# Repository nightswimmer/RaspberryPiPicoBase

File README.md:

# Raspberry Pi Pico Base

A KiCad 10 base design for a custom **RP2354A** board (the RP2350 variant with
2 MB of flash inside the package): everything the chip needs to boot and run
reliably, and nothing else. Fork it, add your own circuitry to the free GPIO,
and order it assembled at JLCPCB.

The design is derived from the official Raspberry Pi
*RP2350A QFN-60 Minimal Design Example* (revision R4-S1, July 2026, MIT
licence, see [NOTICE.md](NOTICE.md)). The external QSPI flash section was
removed because the RP2354A has flash on board, the Micro-USB connector was
replaced by USB-C, and the bill of materials was reworked around JLCPCB's
parts library. The project is self-contained (project-local symbol and
footprint libraries with embedded 3D models) and ERC and DRC pass with zero
violations.

## What is on the board

| Block | Parts |
|---|---|
| MCU | RP2354A (QFN-60, 2 MB internal flash), 12 MHz crystal (YXC X322512MSB4SI, 20 pF) with 33 pF load caps, 1 kΩ series resistor on XOUT. QSPI data/clock pins unused; QSPI_SS kept for BOOTSEL |
| Power | AMS1117-3.3 LDO from USB VBUS, on-chip switching regulator with 3.3 µH inductor for the 1.1 V core, 100 nF decoupling on every supply pin, 33 Ω / 4.7 µF filter on VREG_AVDD |
| USB | USB-C receptacle (Korean Hroparts TYPE-C-31-M-12, USB 2.0), 5.1 kΩ CC pull-downs, 27 Ω series resistors on D+/D- |
| Buttons | BOOTSEL and RUN tactile switches (XKB TS-1187A-B-A-B, 5.1 mm) |
| Debug | 3-pin JST GH SWD connector (Raspberry Pi Debug Probe pinout), not populated by default; SWD/SWCLK are also on the J3 header |
| I/O | Two 2x18 2.54 mm pin headers breaking out all 30 GPIO, 3V3, 1V1 and GND |
| Mechanical | 4 x 2.75 mm mounting holes |

## Bill of materials for JLCPCB

Every part carries its LCSC code (`lcsc_pn` field) and the design uses JLCPCB
*Basic* parts wherever a drop-in exists; the remaining *Extended* parts are the
RP2354A, the inductor, the USB-C connector, the 27 Ω USB resistors and the pin
headers. [docs/BOM.md](docs/BOM.md) has the full sourcing table with
Basic/Extended status, the alternatives that were considered and how to
regenerate the order files. Ready-made files:

- [bom/bom.csv](bom/bom.csv): grouped BOM with designators, quantities and LCSC part numbers
- [bom/cpl.csv](bom/cpl.csv): component placement (DNP parts excluded)

The original Raspberry Pi BOM is in
[docs/reference/RPI-RP2350A-MINIMAL_R4-S1_BOM.md](docs/reference/RPI-RP2350A-MINIMAL_R4-S1_BOM.md)
and the original schematic PDF is next to it.

## Repository layout

```
RaspberryPiPicoBase.kicad_pro   KiCad 10 project
RaspberryPiPicoBase.kicad_sch   schematic (single sheet)
RaspberryPiPicoBase.kicad_pcb   routed 2-layer board, 3D models embedded
sym-lib-table / fp-lib-table    project-local library tables
lib/RaspberryPiPicoBase.kicad_sym    all symbols used by the design
lib/RaspberryPiPicoBase.pretty/      all footprints, each with its 3D model embedded
bom/                            JLCPCB BOM and placement files (generated)
docs/BOM.md                     sourcing table, part status and alternatives
docs/reference/                 original Raspberry Pi schematic PDF and BOM
.mcp.json                       KiCad MCP server for Claude Code (kicad-mcp-pro)
NOTICE.md                       third-party attribution
```

## Requirements

- KiCad 10.0.x (tested with 10.0.8 on Windows 11). No global library setup is
  needed: every symbol, footprint and 3D model lives in this repository.

## Checking the design from the command line

```
kicad-cli sch erc --severity-all RaspberryPiPicoBase.kicad_sch
kicad-cli pcb drc --severity-all --schematic-parity --refill-zones RaspberryPiPicoBase.kicad_pcb
```

Both report zero violations on the base design. The only entries are four
pre-excluded `lib_footprint_mismatch` warnings on the mounting holes, a KiCad
false positive caused by the full-circle arc inside that footprint.

## AI-assisted editing with Claude Code (MCP)

The repository ships a project-local `.mcp.json` that starts
[kicad-mcp-pro](https://github.com/oaslananka/kicad-mcp-pro) 4.5.0 through
`uvx`, in the `full` profile with write mode. Claude Code picks it up
automatically when the repository is the working directory.

Prerequisites:

1. [uv](https://docs.astral.sh/uv/) on the PATH (`uvx` downloads the server on first use).
2. KiCad 10 installed in the default location (kicad-cli is auto-detected).
3. In KiCad: *Preferences > Plugins > Enable KiCad API*, then restart KiCad.

How edits reach KiCad, and what that means for your workflow: tools edit the
`.kicad_sch`, `.kicad_pcb` and library files on disk and verify them with
`kicad-cli`. KiCad does not notice edits made on disk while a file is open, so
after an editing session use *File > Revert* (or reopen the project) before
saving anything in KiCad, otherwise the on-disk changes are overwritten.

## Licence

The project files in this repository are MIT licensed (see [LICENSE](LICENSE)).
The underlying design is copyright Raspberry Pi Ltd, MIT licensed; the
copied KiCad library footprints and 3D model are CC-BY-SA 4.0 with the KiCad
exception; the EasyEDA/LCSC 3D models are included for visualisation (see
[NOTICE.md](NOTICE.md)).

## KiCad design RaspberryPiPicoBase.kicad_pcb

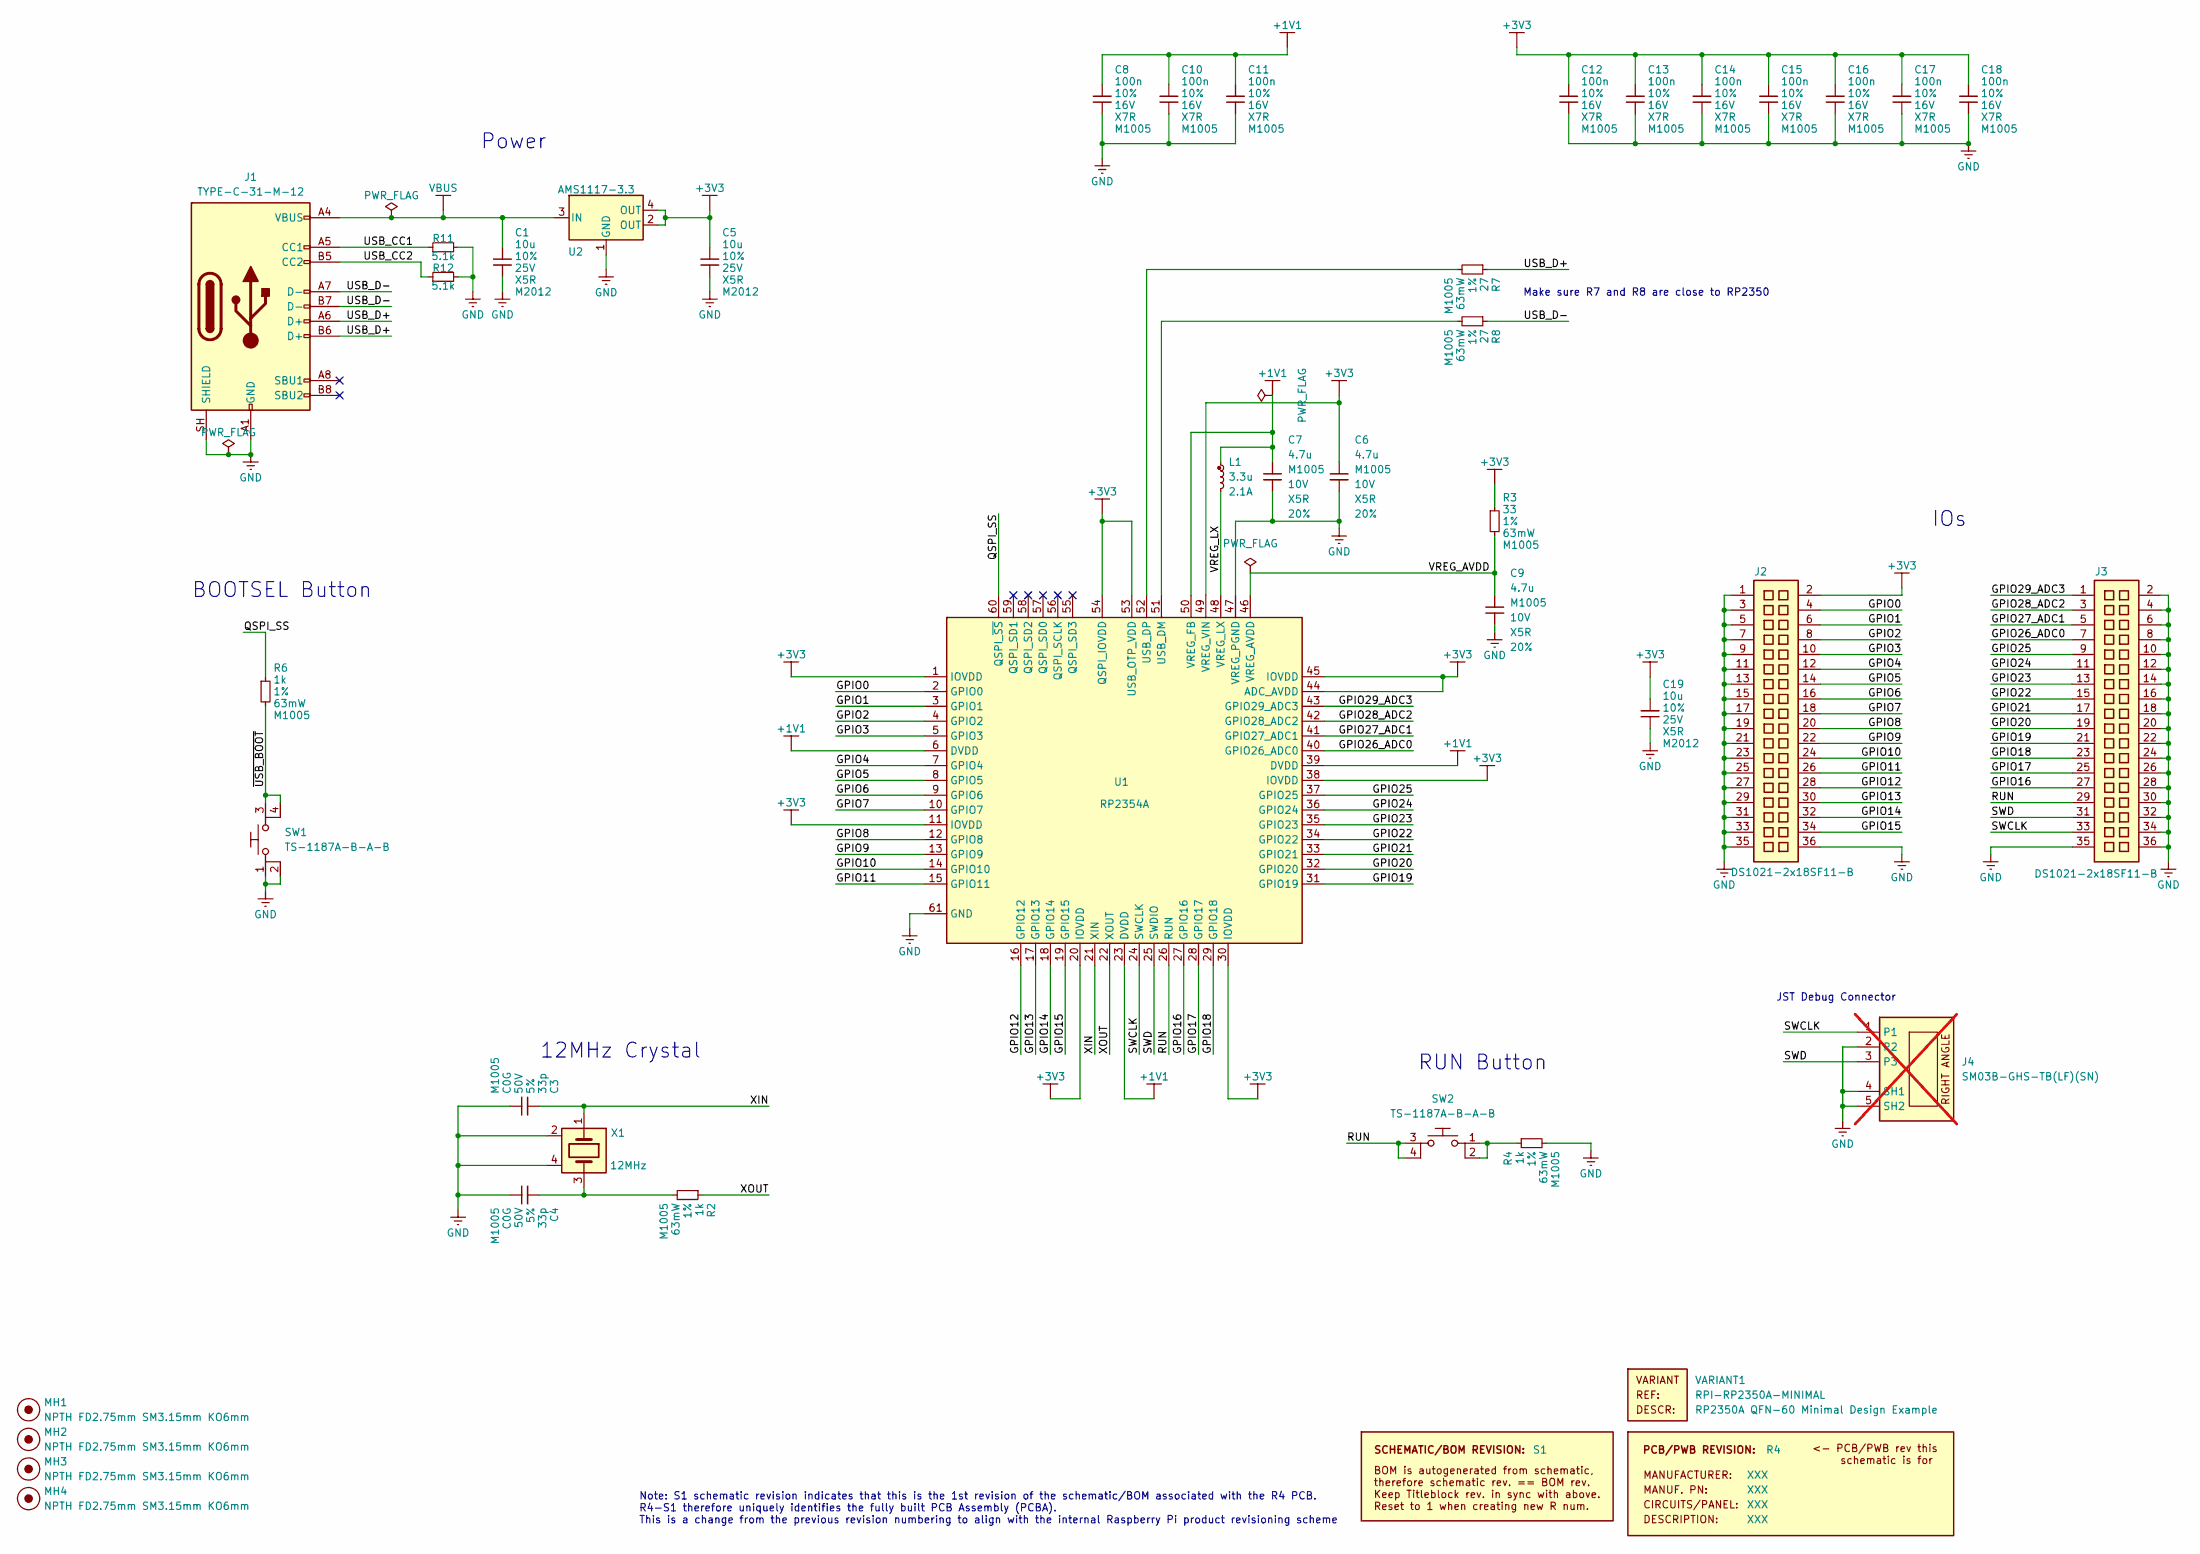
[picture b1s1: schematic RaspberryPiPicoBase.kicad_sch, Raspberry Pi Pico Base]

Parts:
C1, C5, C19: 10u; generic_capc2012x125; voltage 25V; tolerance 10%; part_uid RP-01GYSK-AVBE41; lcsc_pn C15850
C3, C4: 33p; generic_capc1005x50; voltage 50V; tolerance 5%; part_uid RP-01C89W-LLY9XV; lcsc_pn C1562
C6, C7: 4.7u; generic_capc1005x50_wide; voltage 10V; tolerance 20%; part_uid RP-019A1P-0C2GHY; lcsc_pn C23733
C8, C10, C11, C12, C13, C14, C15, C16, C17, C18: 100n; generic_capc1005x50; voltage 16V; tolerance 10%; part_uid RP-01BJ9Y-KRGF41; lcsc_pn C1525
C9: 4.7u; generic_capc1005x50; voltage 10V; tolerance 20%; part_uid RP-019A1P-0C2GHY; lcsc_pn C23733
J1: TYPE-C-31-M-12; USB_C_Receptacle_HRO_TYPE-C-31-M-12; manufacturer_pn TYPE-C-31-M-12; lcsc_pn C165948
J2, J3: DS1021-2x18SF11-B; samtec_tsw-118-07-l-d; part_uid RP-01JWH2-G371Y4; lcsc_pn C7430414
J4: SM03B-GHS-TB(LF)(SN); jst_sm03b-ghs-tb; part_uid RP-01EKJ1-8V9SV1; lcsc_pn C514175; not fitted
L1: 3.3u; abracon_aota-b201610s3r3-101-t; tolerance 20%; part_uid RP-01GY5D-2VC7WP; lcsc_pn C42411119
MH1, MH2, MH3, MH4: NPTH FD2.75mm SM3.15mm KO6mm; none_mh_npth_fd2p75mm_sm3p15mm_ko6mm; part_uid RP-01HF5R-LCTEJS
PCB1: R4; manufacturer_pn XXX
R2, R4, R6: 1k; generic_resc1005x35; tolerance 1%; voltage 50V; part_uid RP-019A1P-4Z6ZWY; lcsc_pn C11702
R3: 33; generic_resc1005x35; tolerance 1%; voltage 50V; part_uid RP-019A1P-58PW9L; lcsc_pn C25105
R7, R8: 27; generic_resc1005x35; tolerance 1%; voltage 50V; part_uid RP-01C89V-LTEYC4; lcsc_pn C25100
R11, R12: 5.1k; generic_resc1005x35; tolerance 1%; manufacturer_pn 0402WGF5101TCE; lcsc_pn C25905
SBREV1: S1
SW1, SW2: TS-1187A-B-A-B; xkb_ts-1187a-b-a-b; part_uid RP-01H0MT-6E9H8F; lcsc_pn C318884
U1: RP2354A; rpi_rp2350a_vias; part_uid RP-01HA9H-9K5E8T; lcsc_pn C41378174
U2: AMS1117-3.3; onsemi_ncp1117st33t3g; voltage 3.3V; part_uid RP-01JWD9-7JRX6J; lcsc_pn C6186
VARIANT1: RPI-RP2350A-MINIMAL
X1: 12MHz; generic_xtalcc320x250x80-4; tolerance 10ppm; part_uid RP-01G8X7-GS352B; lcsc_pn C9002

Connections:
+1V1: C7.1, C8.1, C10.1, C11.1, L1.1, U1.6 (DVDD), U1.23 (DVDD), U1.39 (DVDD), U1.50 (VREG_FB)
+3V3: C5.1, C6.1, C12.1, C13.1, C14.1, C15.1, C16.1, C17.1, C18.1, C19.1, J2.2, R3.1, U1.1 (IOVDD), U1.11 (IOVDD), U1.20 (IOVDD), U1.30 (IOVDD), U1.38 (IOVDD), U1.44 (ADC_AVDD), U1.45 (IOVDD), U1.49 (VREG_VIN), U1.53 (USB_OTP_VDD), U1.54 (QSPI_IOVDD), U2.2 (OUT), U2.4 (OUT)
/GPIO0: J2.4, U1.2 (GPIO0)
/GPIO1: J2.6, U1.3 (GPIO1)
/GPIO2: J2.8, U1.4 (GPIO2)
/GPIO3: J2.10, U1.5 (GPIO3)
/GPIO4: J2.12, U1.7 (GPIO4)
/GPIO5: J2.14, U1.8 (GPIO5)
/GPIO6: J2.16, U1.9 (GPIO6)
/GPIO7: J2.18, U1.10 (GPIO7)
/GPIO8: J2.20, U1.12 (GPIO8)
/GPIO9: J2.22, U1.13 (GPIO9)
/GPIO10: J2.24, U1.14 (GPIO10)
/GPIO11: J2.26, U1.15 (GPIO11)
/GPIO12: J2.28, U1.16 (GPIO12)
/GPIO13: J2.30, U1.17 (GPIO13)
/GPIO14: J2.32, U1.18 (GPIO14)
/GPIO15: J2.34, U1.19 (GPIO15)
/GPIO16: J3.27, U1.27 (GPIO16)
/GPIO17: J3.25, U1.28 (GPIO17)
/GPIO18: J3.23, U1.29 (GPIO18)
/GPIO19: J3.21, U1.31 (GPIO19)
/GPIO20: J3.19, U1.32 (GPIO20)
/GPIO21: J3.17, U1.33 (GPIO21)
/GPIO22: J3.15, U1.34 (GPIO22)
/GPIO23: J3.13, U1.35 (GPIO23)
/GPIO24: J3.11, U1.36 (GPIO24)
/GPIO25: J3.9, U1.37 (GPIO25)
/GPIO26_ADC0: J3.7, U1.40 (GPIO26_ADC0)
/GPIO27_ADC1: J3.5, U1.41 (GPIO27_ADC1)
/GPIO28_ADC2: J3.3, U1.42 (GPIO28_ADC2)
/GPIO29_ADC3: J3.1, U1.43 (GPIO29_ADC3)
/QSPI_SS: R6.1, U1.60 (QSPI_~SS)
/RUN: J3.29, SW2.3, SW2.4, U1.26 (RUN)
/SWCLK: J3.33, J4.1, U1.24 (SWCLK)
/SWD: J3.31, J4.3, U1.25 (SWDIO)
/USB_CC1: J1.A5 (CC1), R11.1
/USB_CC2: J1.B5 (CC2), R12.1
/USB_D+: J1.A6 (D+), J1.B6 (D+), R7.1
/USB_D-: J1.A7 (D-), J1.B7 (D-), R8.1
/VREG_AVDD: C9.1, R3.2, U1.46 (VREG_AVDD)
/VREG_LX: L1.2, U1.48 (VREG_LX)
/XIN: C3.1, U1.21 (XIN), X1.1
/XOUT: R2.1, U1.22 (XOUT)
/~USB_BOOT: R6.2, SW1.3, SW1.4
GND: C1.2, C3.2, C4.2, C5.2, C6.2, C7.2, C8.2, C9.2, C10.2, C11.2, C12.2, C13.2, C14.2, C15.2, C16.2, C17.2, C18.2, C19.2, J1.A1 (GND), J1.A12 (GND), J1.B1 (GND), J1.B12 (GND), J1.SH (SHIELD), J2.1, J2.3, J2.5, J2.7, J2.9, J2.11, J2.13, J2.15, J2.17, J2.19, J2.21, J2.23, J2.25, J2.27, J2.29, J2.31, J2.33, J2.35, J2.36, J3.2, J3.4, J3.6, J3.8, J3.10, J3.12, J3.14, J3.16, J3.18, J3.20, J3.22, J3.24, J3.26, J3.28, J3.30, J3.32, J3.34, J3.35, J3.36, J4.2, J4.4 (SH1), J4.5 (SH2), R4.2, R11.2, R12.2, SW1.1, SW1.2, U1.47 (VREG_PGND), U1.61 (GND), U2.1 (GND), X1.2, X1.4
unnamed: C4.1, R2.2, X1.3
unnamed: R4.1, SW2.1, SW2.2
unnamed: R8.2, U1.51 (USB_DM)
unnamed: R7.2, U1.52 (USB_DP)
VBUS: C1.1, J1.A4 (VBUS), J1.A9 (VBUS), J1.B4 (VBUS), J1.B9 (VBUS), U2.3 (IN)

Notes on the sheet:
JST Debug Connector
IOs
RUN Button
BOOTSEL Button
Note: S1 schematic revision indicates that this is the 1st revision of the schematic/BOM associated with the R4 PCB. R4-S1 therefore uniquely identifies the fully built PCB Assembly (PCBA). This is a change from the previous revision numbering to align with the internal Raspberry Pi product revisio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
Make sure R7 and R8 are close to RP2350
12MHz Crystal
Power

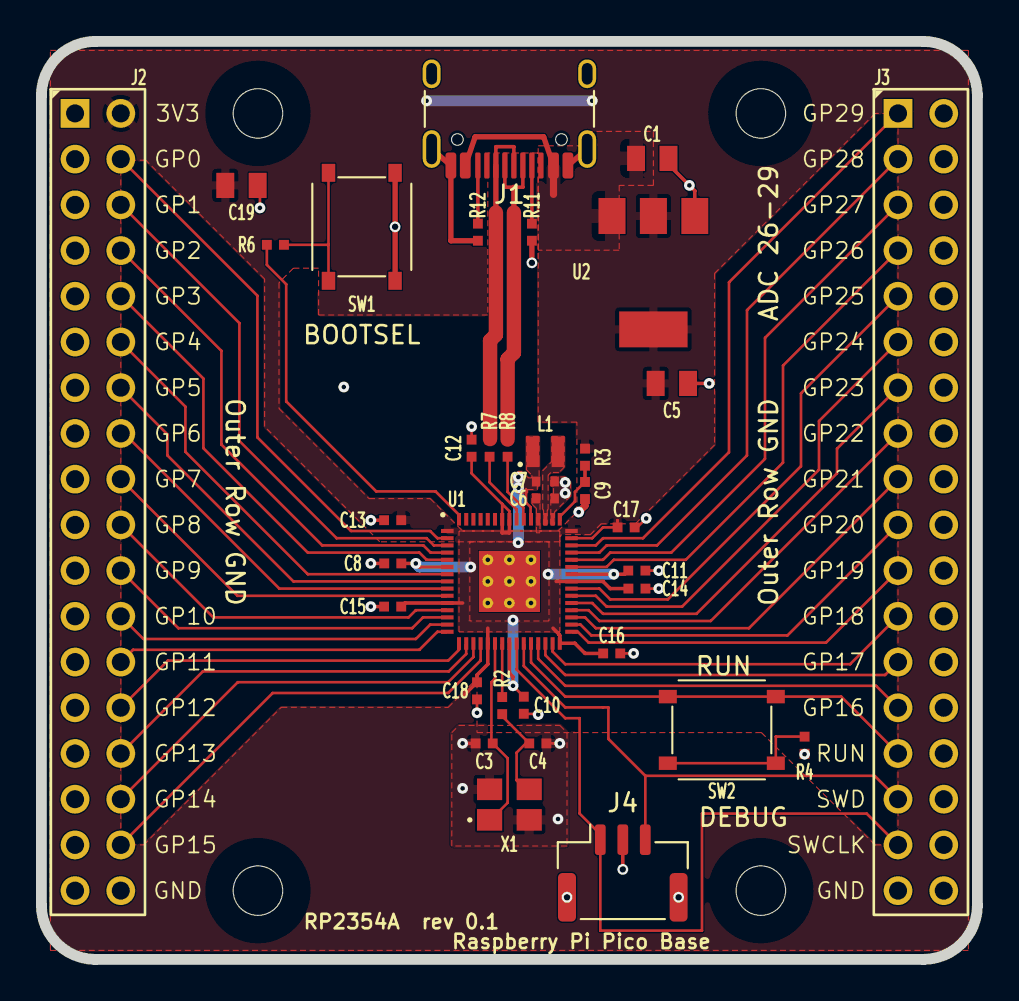
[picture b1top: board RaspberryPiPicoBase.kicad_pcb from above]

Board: 2 copper layers, 52.0 x 51.0 mm, 40 parts (0 on the bottom side), 51 nets.

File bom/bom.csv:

"Designator","Quantity","Value","Footprint","Manufacturer","Manufacturer Part","LCSC Part #","Description"
"C1,C5,C19","3","10u","RaspberryPiPicoBase:generic_capc2012x125","Samsung Electro-Mechanics","CL21A106KAYNNNE","C15850","Capacitor, MLCC, 10uF, 10%, M2012, 25V, X5R"
"C3,C4","2","33p","RaspberryPiPicoBase:generic_capc1005x50","FH (Guangdong Fenghua Advanced Tech)","0402CG330J500NT","C1562","Capacitor, MLCC, 33pF, 5%, M1005, 50V, C0G"
"C6,C7","2","4.7u","RaspberryPiPicoBase:generic_capc1005x50_wide","Samsung Electro-Mechanics","CL05A475MP5NRNC","C23733","Capacitor, MLCC, 4.7uF, 20%, M1005, 10V, X5R"
"C8,C10-C18","10","100n","RaspberryPiPicoBase:generic_capc1005x50","Samsung Electro-Mechanics","CL05B104KO5NNNC","C1525","Capacitor, MLCC, 100nF, 10%, M1005, 16V, X7R"
"C9","1","4.7u","RaspberryPiPicoBase:generic_capc1005x50","Samsung Electro-Mechanics","CL05A475MP5NRNC","C23733","Capacitor, MLCC, 4.7uF, 20%, M1005, 10V, X5R"
"J1","1","TYPE-C-31-M-12","RaspberryPiPicoBase:USB_C_Receptacle_HRO_TYPE-C-31-M-12","Korean Hroparts Elec","TYPE-C-31-M-12","C165948","USB-C Receptacle, USB 2.0, 16P, SMD, Right Angle, Korean Hroparts TYPE-C-31-M-12"
"J2,J3","2","DS1021-2x18SF11-B","RaspberryPiPicoBase:samtec_tsw-118-07-l-d","CONNFLY Elec","DS1021-2x18SF11-B","C7430414","Pin Header, 02x18W, 2.54mm, PTH, Male"
"L1","1","3.3u","RaspberryPiPicoBase:abracon_aota-b201610s3r3-101-t","Abracon","AOTA-B201610S3R3-101-T","C42411119","Inductor, SMT, 3.3uH, 20%, Irms=2.1A, Isat=2.4A, DCR=115mR typ 140mR max, Polarity Marked, M2016"
"R2,R4,R6","3","1k","RaspberryPiPicoBase:generic_resc1005x35","UNI-ROYAL (Uniroyal Elec)","0402WGF1001TCE","C11702","Resistor, Chip, 1kR, M1005, 63mW, 1%"
"R3","1","33","RaspberryPiPicoBase:generic_resc1005x35","UNI-ROYAL (Uniroyal Elec)","0402WGF330JTCE","C25105","Resistor, Chip, 33R, M1005, 63mW, 1%"
"R7,R8","2","27","RaspberryPiPicoBase:generic_resc1005x35","UNI-ROYAL (Uniroyal Elec)","0402WGF270JTCE","C25100","Resistor, Chip, 27R, M1005, 63mW, 1%"
"R11,R12","2","5.1k","RaspberryPiPicoBase:generic_resc1005x35","UNI-ROYAL (Uniroyal Elec)","0402WGF5101TCE","C25905","Resistor, Chip, 5.1kR, M1005, 63mW, 1%"
"SW1,SW2","2","TS-1187A-B-A-B","RaspberryPiPicoBase:xkb_ts-1187a-b-a-b","XKB Connection","TS-1187A-B-A-B","C318884","Tactile Pushbutton, SPST, N.O., 5.1x5.1x1.5mm, 160gf"
"U1","1","RP2354A","RaspberryPiPicoBase:rpi_rp2350a_vias","Raspberry Pi","RP2354A","C41378174","RP2354A MCU, Dual Cortex M33/Hazard3, 2 MB internal flash, QFN-60"
"U2","1","AMS1117-3.3","RaspberryPiPicoBase:onsemi_ncp1117st33t3g","Advanced Monolithic Systems","AMS1117-3.3","C6186","LDO, Vin=4.75-15V, Vout=3.3V, 1A, SOT-223"
"X1","1","12MHz","RaspberryPiPicoBase:generic_xtalcc320x250x80-4","YXC Crystal Oscillators","X322512MSB4SI","C9002","XTAL, SMT, 12 MHz, Fundamental, Ftol=10ppm, Fstab=20ppm, 20pF, ESR 80R max, 3.2x2.5mm"
